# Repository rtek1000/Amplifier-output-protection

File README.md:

# Amplifier-output-protection
Thermal protection for class AB amplifier output transistors

- Most class AB amplifiers built with NPN and PNP transistors are very poor in protection.
- - Some designs put a simple current limiter, but this does not guarantee the thermal protection of the transistor.
- - Some amplifier manufacturers use a fixed mechanical thermostat of about 100°C against the heatsink.

The partial scheme of an amplifier can be seen below,
- Where there is the current limiting transistor (T10),
- The resistor 0R33 (R37) serves as a reference to monitor the current of the output transistor (T16).
- The other output transistors (T18, T20) are not monitored.
- In this type of circuit, all transistors are expected to have a similar current gain.

------

The circuit of Thermal protection is based on the TL431 which is widely used in switching power supplies, this IC is very reliable:
- Each output transistor must have a 10k B3950 NTC sensor.
- The relay output can be used to jumper the signal input of amplifier.

The main schematic shows several blocks "NTC_sensor" so that each transistor can be monitored independently:
- If the amplifier has 20 output transistors, 20 blocks are needed.

To fix the NTC on the transistor, STARS-922 thermal glue can be used.

## Licence:
- Hardware:

Released under CERN OHL 1.2: https://ohwr.org/cernohl

- This library is distributed in the hope that it will be useful, but WITHOUT ANY WARRANTY; without even the implied warranty of MERCHANTABILITY or FITNESS FOR A PARTICULAR PURPOSE.

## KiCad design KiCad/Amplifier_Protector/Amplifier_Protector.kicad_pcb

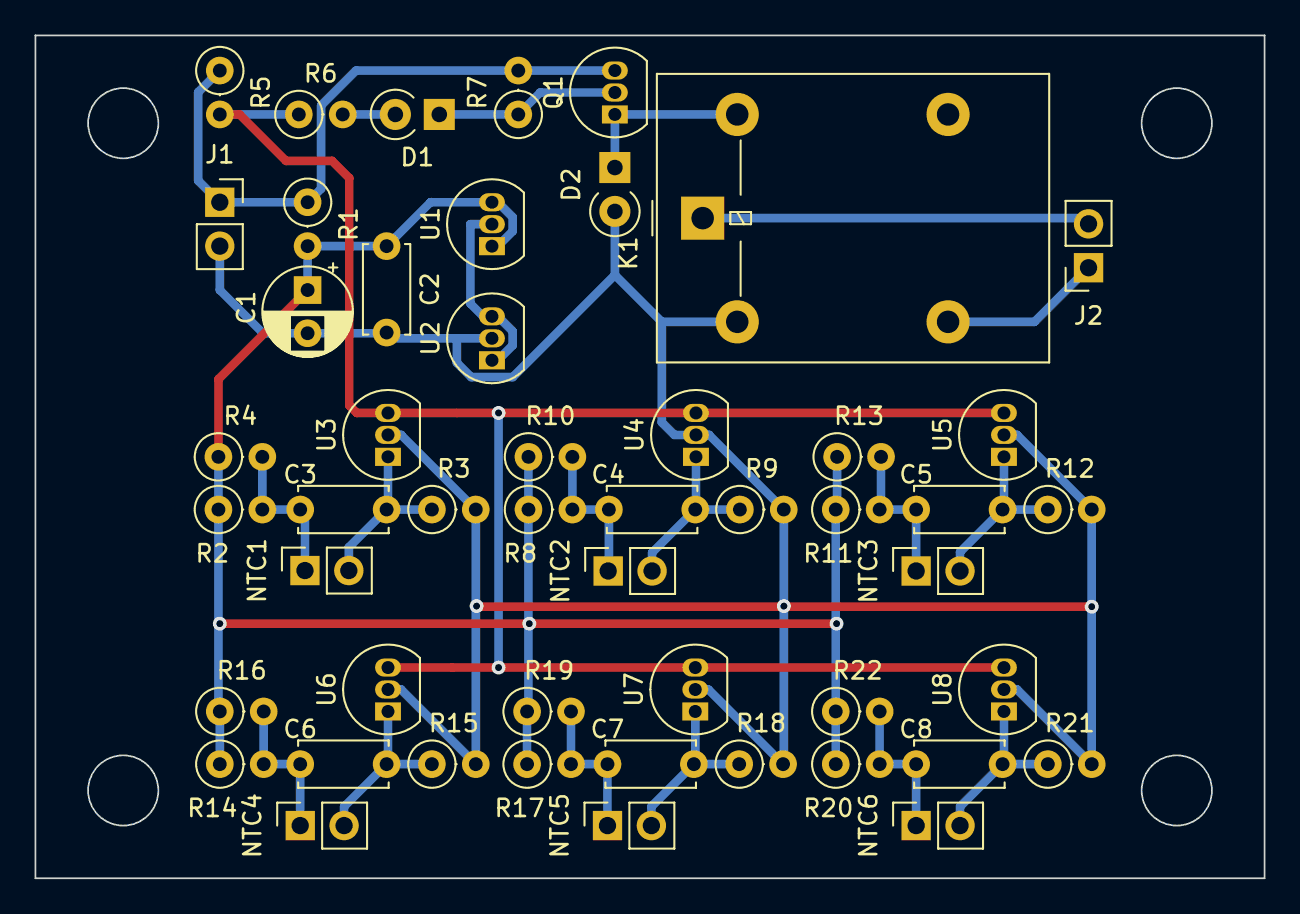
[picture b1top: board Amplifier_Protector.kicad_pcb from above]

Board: 2 copper layers, 71.1 x 48.8 mm, 50 parts (0 on the bottom side), 22 nets.

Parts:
C1: 10u; CP_Radial_D5.0mm_P2.50mm
C2: 100n; C_Disc_D5.0mm_W2.5mm_P5.00mm
C3, C4, C5, C6, C7, C8: 10n; C_Disc_D5.0mm_W2.5mm_P5.00mm
D1: BZV55C5V1; D_A-405_P2.54mm_Vertical_KathodeUp
D2: 1N4148; D_A-405_P2.54mm_Vertical_KathodeUp
J1: 12V; PinSocket_1x02_P2.54mm_Vertical
J2: OUT; PinSocket_1x02_P2.54mm_Vertical
K1: G5LE-1; Relay_SPDT_Omron-G5LE-1
NTC1, NTC2, NTC3, NTC4, NTC5, NTC6: 10k; PinSocket_1x02_P2.54mm_Vertical
Q1: BC328; TO-92_Inline
R1: 470; R_Axial_DIN0207_L6.3mm_D2.5mm_P2.54mm_Vertical
R2, R3, R7, R8, R9, R11, R12, R14, R15, R17, R18, R20, R21: 10k; R_Axial_DIN0207_L6.3mm_D2.5mm_P2.54mm_Vertical
R4, R10, R13, R16, R19, R22: 120k; R_Axial_DIN0207_L6.3mm_D2.5mm_P2.54mm_Vertical
R5, R6: 1k; R_Axial_DIN0207_L6.3mm_D2.5mm_P2.54mm_Vertical
U1, U2, U3, U4, U5, U6, U7, U8: TL431LP; TO-92_Inline

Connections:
+12V: J1.1, Q1.3 (E), R1.1, R5.1, R7.2
GND: C1.2, C2.2, D2.2 (A), J1.2, K1.2, R3.2, R9.2, R12.2, R15.2, R18.2, R21.2, U2.2 (A), U3.2 (A), U4.2 (A), U5.2 (A), U6.2 (A), U7.2 (A), U8.2 (A)
unnamed: D1.2 (A), R6.2
unnamed: D1.1 (K), Q1.2 (B), R7.1
unnamed: D2.1 (K), K1.5, Q1.1 (C)
unnamed: J2.1, K1.3
unnamed: J2.2, K1.1
unnamed: C3.1, NTC1.1, R2.2, R4.2
unnamed: C3.2, NTC1.2, R3.1, U3.1 (REF)
unnamed: C4.1, NTC2.1, R8.2, R10.2
unnamed: C4.2, NTC2.2, R9.1, U4.1 (REF)
unnamed: C5.1, NTC3.1, R11.2, R13.2
unnamed: C5.2, NTC3.2, R12.1, U5.1 (REF)
unnamed: C6.1, NTC4.1, R14.2, R16.2
unnamed: C6.2, NTC4.2, R15.1, U6.1 (REF)
unnamed: C7.1, NTC5.1, R17.2, R19.2
unnamed: C7.2, NTC5.2, R18.1, U7.1 (REF)
unnamed: C8.1, NTC6.1, R20.2, R22.2
unnamed: C8.2, NTC6.2, R21.1, U8.1 (REF)
unnamed: U1.2 (A), U2.1 (REF), U2.3 (K)
OUT: R5.2, R6.1, U3.3 (K), U4.3 (K), U5.3 (K), U6.3 (K), U7.3 (K), U8.3 (K)
V5: C1.1, C2.1, R1.2, R2.1, R4.1, R8.1, R10.1, R11.1, R13.1, R14.1, R16.1, R17.1, R19.1, R20.1, R22.1, U1.1 (REF), U1.3 (K)

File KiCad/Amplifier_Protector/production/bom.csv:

Designator,Footprint,Quantity,Value,LCSC Part #
C1,CP_Radial_D5.0mm_P2.50mm,1,10u,
C2,C_Disc_D5.0mm_W2.5mm_P5.00mm,1,100n,
"C3, C4, C5, C6, C7, C8",C_Disc_D5.0mm_W2.5mm_P5.00mm,6,10n,
D1,D_A-405_P2.54mm_Vertical_KathodeUp,1,BZV55C5V1,
D2,D_A-405_P2.54mm_Vertical_KathodeUp,1,1N4148,
J1,PinSocket_1x02_P2.54mm_Vertical,1,12V,
J2,PinSocket_1x02_P2.54mm_Vertical,1,OUT,
K1,Relay_SPDT_Omron-G5LE-1,1,G5LE-1,
"NTC1, NTC2, NTC3, NTC4, NTC5, NTC6",PinSocket_1x02_P2.54mm_Vertical,6,10k,
Q1,TO-92_Inline,1,BC328,
R1,R_Axial_DIN0207_L6.3mm_D2.5mm_P2.54mm_Vertical,1,470,
"R10, R13, R16, R19, R22, R4",R_Axial_DIN0207_L6.3mm_D2.5mm_P2.54mm_Vertical,6,120k,
"R11, R12, R14, R15, R17, R18, R2, R20, R21, R3, R7, R8, R9",R_Axial_DIN0207_L6.3mm_D2.5mm_P2.54mm_Vertical,13,10k,
"R5, R6",R_Axial_DIN0207_L6.3mm_D2.5mm_P2.54mm_Vertical,2,1k,
"U1, U2, U3, U4, U5, U6, U7, U8",TO-92_Inline,8,TL431LP,
